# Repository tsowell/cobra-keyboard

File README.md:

(Vezi [README-ro.md](README-ro.md) pentru o traducere greșită în română.)

# Cobra keyboard

These are KiCad files for a keyboard for the [Cobra
computer](http://cobrasov.com).  It is adapted from the [version 1.0 keyboard
on cobrasov.com](http://cobrasov.com/CoBra%20Project/kbd1.0.html).

The changes were necessary to adapt the design to the orientation and sizes of
my [custom keycaps](https://github.com/tsowell/cobra-keycaps).

NOTE: This revision has not been tested yet.  After I ordered the PCB for the
[previous revision][b5ad87d], I decided to swap the locations of the GRAPH and
NEW MODE keys.

[b5ad87d]: https://github.com/tsowell/cobra-keyboard/tree/b5ad87d

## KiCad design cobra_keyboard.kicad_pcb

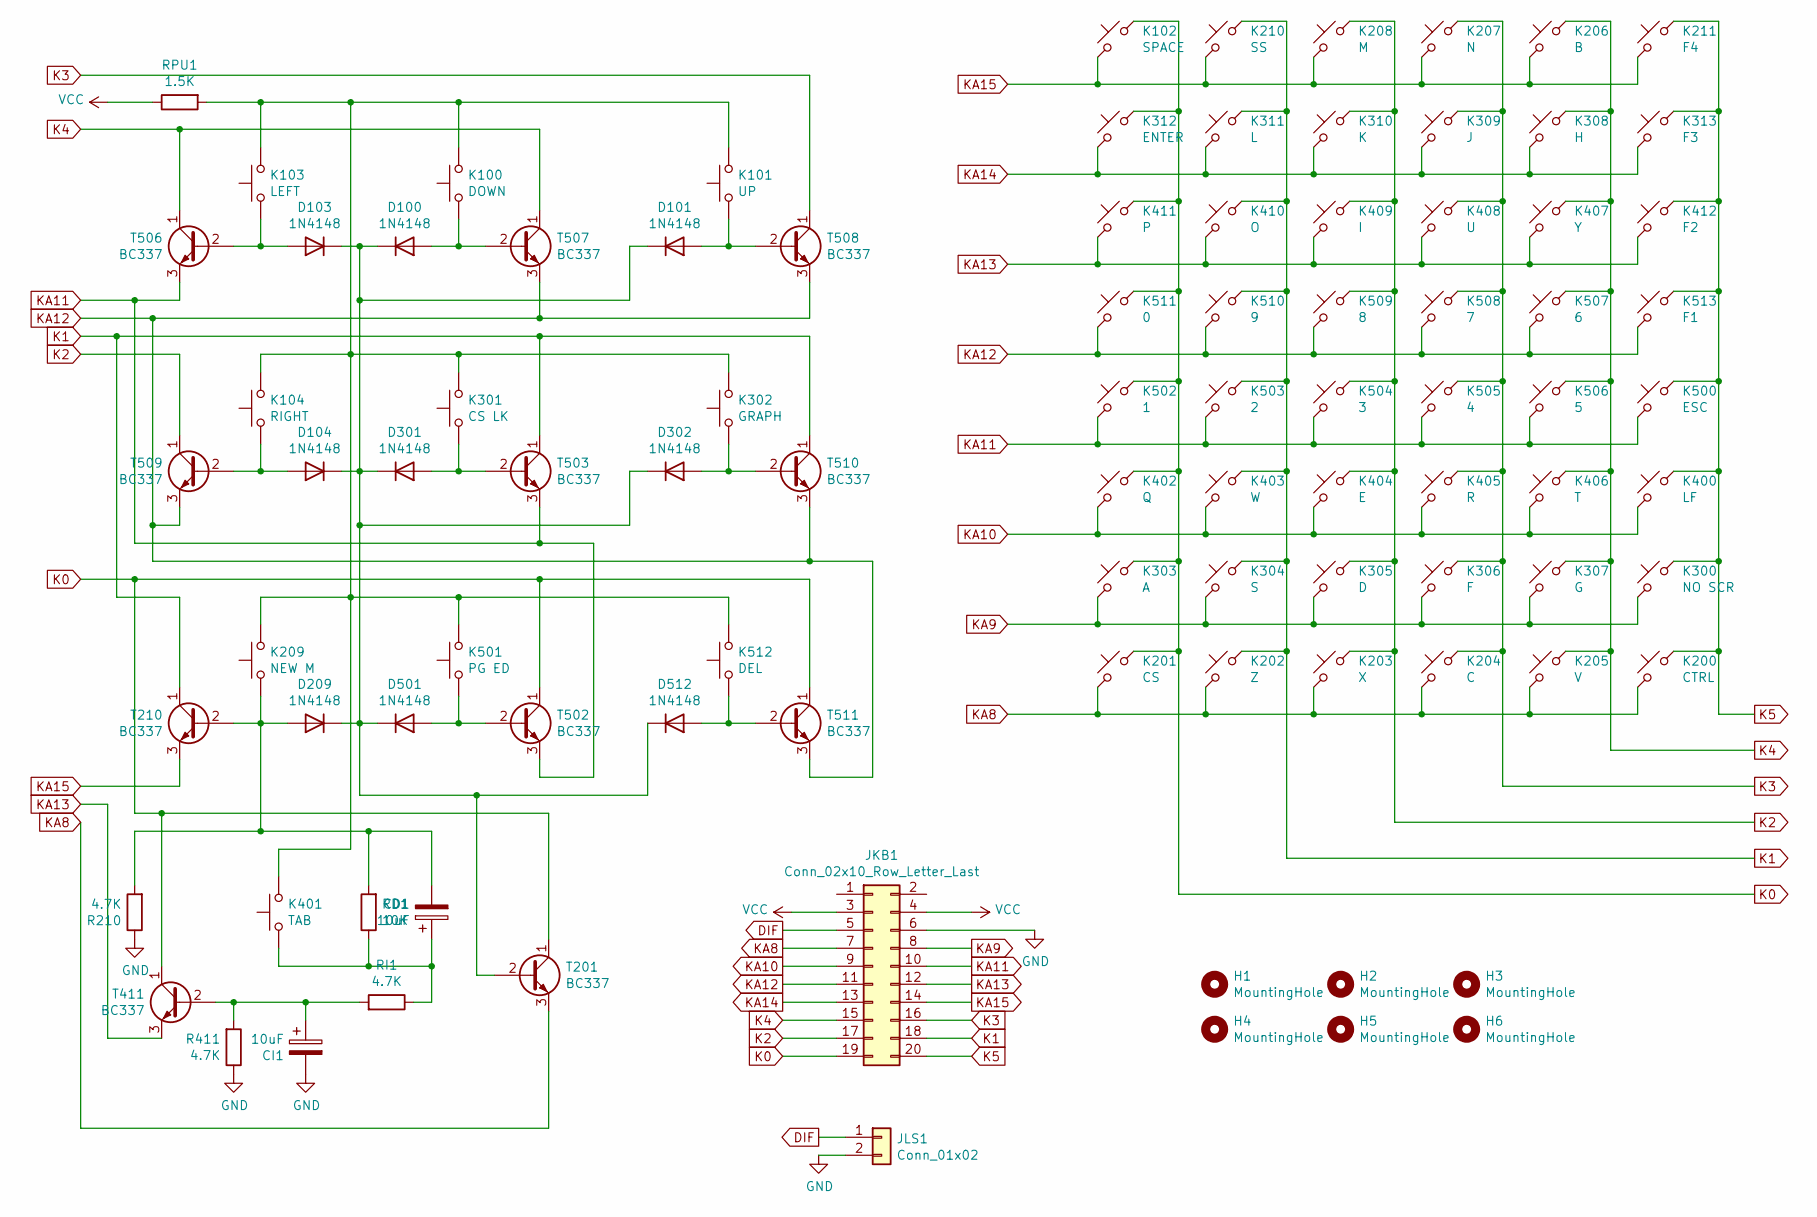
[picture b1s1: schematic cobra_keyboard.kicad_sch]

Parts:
CD1: 10uF; CP_Radial_D4.0mm_P1.50mm_Horizontal
CI1: 10uF; CP_Radial_D4.0mm_P1.50mm_Horizontal
D100, D101, D103, D104, D209, D301, D302, D501, D512: 1N4148; D_DO-35_SOD27_P7.62mm_Horizontal
H1, H2, H3, H4, H5, H6: MountingHole; MountingHole_3mm
JKB1: Conn_02x10_Row_Letter_Last; PinHeader_2x10_P2.54mm_Vertical
JLS1: Conn_01x02; PinHeader_1x02_P2.54mm_Vertical
K100: DOWN; SW_Cherry_MX_1.00u_PCB
K101: UP; SW_Cherry_MX_1.00u_PCB
K102: SPACE; SW_Cherry_MX_6.25u_PCB
K103: LEFT; SW_Cherry_MX_1.00u_PCB
K104: RIGHT; SW_Cherry_MX_1.00u_PCB
K200: CTRL; SW_Cherry_MX_1.00u_PCB
K201: CS; SW_Cherry_MX_2.25u_PCB
K202: Z; SW_Cherry_MX_1.00u_PCB
K203: X; SW_Cherry_MX_1.00u_PCB
K204: C; SW_Cherry_MX_1.00u_PCB
K205: V; SW_Cherry_MX_1.00u_PCB
K206: B; SW_Cherry_MX_1.00u_PCB
K207: N; SW_Cherry_MX_1.00u_PCB
K208: M; SW_Cherry_MX_1.00u_PCB
K209: NEW M; SW_Cherry_MX_1.00u_PCB
K210: SS; SW_Cherry_MX_2.75u_PCB
K211: F4; SW_Cherry_MX_1.00u_PCB
K300: NO SCR; SW_Cherry_MX_1.00u_PCB
K301: CS LK; SW_Cherry_MX_1.75u_PCB
K302: GRAPH; SW_Cherry_MX_1.50u_PCB
K303: A; SW_Cherry_MX_1.00u_PCB
K304: S; SW_Cherry_MX_1.00u_PCB
K305: D; SW_Cherry_MX_1.00u_PCB
K306: F; SW_Cherry_MX_1.00u_PCB
K307: G; SW_Cherry_MX_1.00u_PCB
K308: H; SW_Cherry_MX_1.00u_PCB
K309: J; SW_Cherry_MX_1.00u_PCB
K310: K; SW_Cherry_MX_1.00u_PCB
K311: L; SW_Cherry_MX_1.00u_PCB
K312: ENTER; SW_Cherry_MX_2.25u_PCB
K313: F3; SW_Cherry_MX_1.00u_PCB
K400: LF; SW_Cherry_MX_1.00u_PCB
K401: TAB; SW_Cherry_MX_1.50u_PCB
K402: Q; SW_Cherry_MX_1.00u_PCB
K403: W; SW_Cherry_MX_1.00u_PCB
K404: E; SW_Cherry_MX_1.00u_PCB
K405: R; SW_Cherry_MX_1.00u_PCB
K406: T; SW_Cherry_MX_1.00u_PCB
K407: Y; SW_Cherry_MX_1.00u_PCB
K408: U; SW_Cherry_MX_1.00u_PCB
K409: I; SW_Cherry_MX_1.00u_PCB
K410: O; SW_Cherry_MX_1.00u_PCB
K411: P; SW_Cherry_MX_1.00u_PCB
K412: F2; SW_Cherry_MX_1.00u_PCB
K500: ESC; SW_Cherry_MX_1.00u_PCB
K501: PG ED; SW_Cherry_MX_1.00u_PCB
K502: 1; SW_Cherry_MX_1.00u_PCB
K503: 2; SW_Cherry_MX_1.00u_PCB
K504: 3; SW_Cherry_MX_1.00u_PCB
K505: 4; SW_Cherry_MX_1.00u_PCB
K506: 5; SW_Cherry_MX_1.00u_PCB
K507: 6; SW_Cherry_MX_1.00u_PCB
K508: 7; SW_Cherry_MX_1.00u_PCB
K509: 8; SW_Cherry_MX_1.00u_PCB
K510: 9; SW_Cherry_MX_1.00u_PCB
K511: 0; SW_Cherry_MX_1.00u_PCB
K512: DEL; SW_Cherry_MX_2.00u_PCB
K513: F1; SW_Cherry_MX_1.00u_PCB
R210, R411: 4.7K; R_Axial_DIN0204_L3.6mm_D1.6mm_P7.62mm_Horizontal
RD1: 10K; R_Axial_DIN0204_L3.6mm_D1.6mm_P7.62mm_Horizontal
RI1: 4.7K; R_Axial_DIN0204_L3.6mm_D1.6mm_P7.62mm_Horizontal
RPU1: 1.5K; R_Axial_DIN0204_L3.6mm_D1.6mm_P7.62mm_Horizontal
T201, T210, T411, T502, T503, T506, T507, T508, T509, T510, T511: BC337; TO-92_Inline_Wide_Horizontal1

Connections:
DIF: JKB1.5, JLS1.1
GND: CI1.2, JKB1.6, JLS1.2, R210.1, R411.1
K0: JKB1.19, K102.2, K201.2, K303.2, K312.2, K402.2, K411.2, K502.2, K511.2, T201.1 (C), T411.1 (C), T502.1 (C), T511.1 (C)
K1: JKB1.18, K202.2, K210.2, K304.2, K311.2, K403.2, K410.2, K503.2, K510.2, T210.1 (C), T503.1 (C), T510.1 (C)
K2: JKB1.17, K203.2, K208.2, K305.2, K310.2, K404.2, K409.2, K504.2, K509.2, T509.1 (C)
K3: JKB1.16, K204.2, K207.2, K306.2, K309.2, K405.2, K408.2, K505.2, K508.2, T508.1 (C)
K4: JKB1.15, K205.2, K206.2, K307.2, K308.2, K406.2, K407.2, K506.2, K507.2, T506.1 (C), T507.1 (C)
K5: JKB1.20, K200.2, K211.2, K300.2, K313.2, K400.2, K412.2, K500.2, K513.2
KA8: JKB1.7, K200.1, K201.1, K202.1, K203.1, K204.1, K205.1, T201.3 (E)
KA9: JKB1.8, K300.1, K303.1, K304.1, K305.1, K306.1, K307.1
KA10: JKB1.9, K400.1, K402.1, K403.1, K404.1, K405.1, K406.1
KA11: JKB1.10, K500.1, K502.1, K503.1, K504.1, K505.1, K506.1, T502.3 (E), T503.3 (E), T506.3 (E)
KA12: JKB1.11, K507.1, K508.1, K509.1, K510.1, K511.1, K513.1, T507.3 (E), T508.3 (E), T509.3 (E), T510.3 (E), T511.3 (E)
KA13: JKB1.12, K407.1, K408.1, K409.1, K410.1, K411.1, K412.1, T411.3 (E)
KA14: JKB1.13, K308.1, K309.1, K310.1, K311.1, K312.1, K313.1
KA15: JKB1.14, K102.1, K206.1, K207.1, K208.1, K210.1, K211.1, T210.3 (E)
unnamed: CD1.1, K401.1, RD1.1, RI1.1
unnamed: CD1.2, D209.2 (A), K209.1, R210.2, RD1.2, T210.2 (B)
unnamed: CI1.1, R411.2, RI1.2, T411.2 (B)
unnamed: D100.1 (K), D101.1 (K), D103.1 (K), D104.1 (K), D209.1 (K), D301.1 (K), D302.1 (K), D501.1 (K), D512.1 (K), T201.2 (B)
unnamed: D100.2 (A), K100.1, T507.2 (B)
unnamed: D101.2 (A), K101.1, T508.2 (B)
unnamed: D103.2 (A), K103.1, T506.2 (B)
unnamed: D104.2 (A), K104.1, T509.2 (B)
unnamed: D301.2 (A), K301.1, T503.2 (B)
unnamed: D302.2 (A), K302.1, T510.2 (B)
unnamed: D501.2 (A), K501.1, T502.2 (B)
unnamed: D512.2 (A), K512.1, T511.2 (B)
unnamed: K100.2, K101.2, K103.2, K104.2, K209.2, K301.2, K302.2, K401.2, K501.2, K512.2, RPU1.2
VCC: JKB1.3, JKB1.4, RPU1.1

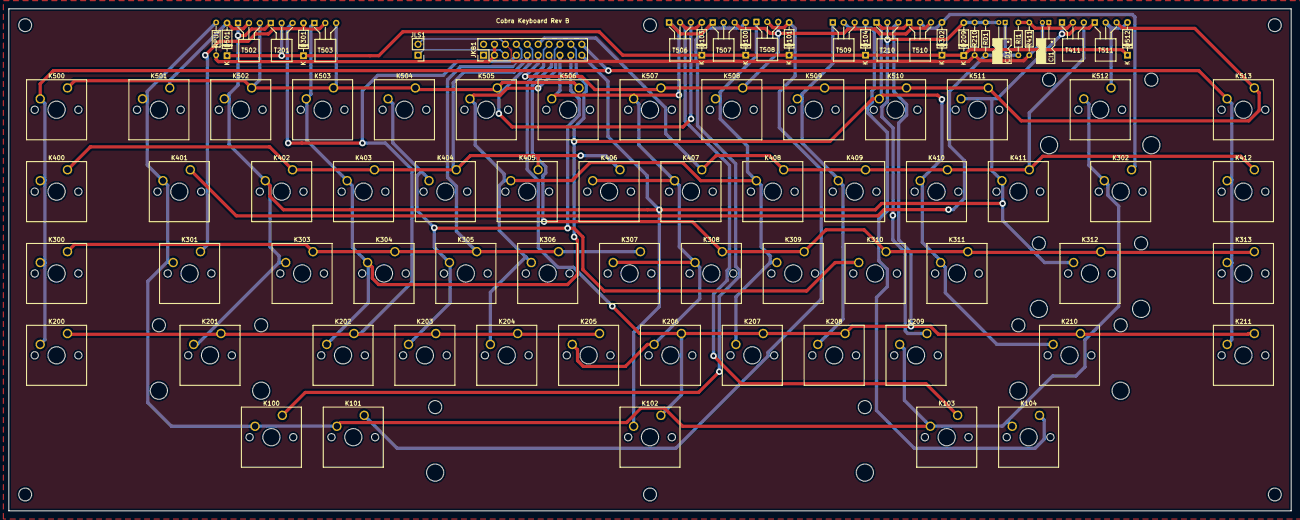
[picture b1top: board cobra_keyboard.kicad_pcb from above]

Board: 2 copper layers, 298.4 x 116.8 mm, 93 parts (0 on the bottom side), 30 nets.

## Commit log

2022-08-23 Add .gitignore
2022-08-24 Swap GRAPH and NEW MODE keys
